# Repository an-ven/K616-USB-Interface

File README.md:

# K616 USB Interface board

Arduino based USB interface board for Keithley 616 digital electrometer. Somewhat inspired by Keithley 6162 Isolated Output and Control module, but with a modern computer interface.

## Firmware features

- Presents a common USB serial interface
- Measurement capture using hardware counter and interrupts
- Instrument control (Remote zero check, Sensitivity selection and Display hold)
- Continuous or single measurement output
- Compact and human readable output formats
- Mostly single character commands for instrument and interface control
- Interface settings can be saved to load on next power up

## Hardware features

- Optically isolated inputs and outputs
- Mounts inside the instrument with USB port accessible on the back panel
- Fits on to K6162 interface pins headers (J113, J114 and J115) on the main board

# Measurement output

Output strings consist of three parts separated by space characters: 
- a float type number representing the measured value
- units of the measured value
- instrument state indicators

In normal or "compact" output mode (selected by sending `u` command character) the number mirrors the instrument display, where sensitivity setting directly determines the number of decimal places of mantissa and the exponent is determined form range switch position. Units are also determined by range switch position. Instrument state indicators are printed as single characters:
- `N` ... Normal operation
- `O` ... Overflow
- `Z` ... Zero Check
- `R` ... Remote Zero Check
- `A` ... Auto sensitivity
- `M` ... Manual sensitivity
- `n` ... Sensitivity range number where `n={1,2,3,4,5}`
- `H` ... Display hold enabled 
- `E` ... Count error (instrument probably off)

In human friendly output mode (selected by sending `U` command character) the number of decimal places and unit prefix are determined based on what is most appropriate for currently selected range and sensitivity settings. The instrument state indicator characters get replaced by whole words separated by space characters.

## Example outputs strings

Normal operation (measuring resistance, automatic sensitivity):

    +0.993E9 Ohm NA3

Human friendly unit display (same conditions as above):

    +0.992 GOhm Normal Auto Sensitivity=3

Remote zero check enabled:

    -0.00000E-6 A ZRA1

    -0.00 nA Zero Remote Auto Sensitivity=1

Overflow condition, manual sensitivity:

    +0.2016E0 V OM2

    +201.6 mV Overflow Manual Sensitivity=2

Instrument powered off (no "gated clock" and "count now" signals detected)

    -999.9E-6 A E

    -999.9 uA Count Error

# Command set

The interface board can be controlled using mostly single character commands, exception being the sensitivity select command which consists of two characters.

## Instrument control:

`Z|z`: Remote zero check (upper case to enable, lower case to disable)

`H|h`: Instrument display hold (upper case to enable, lower case to disable)

`r[x]`: Sensitivity select, where [x] is a number representing different sensitivity settings:
- 0 ... Auto sensitivity
- 1 ... 0,01 full scale
- 2 ... 0,1 full scale
- 3 ... 1 full scale
- 4 ... 10 full scale
- 5 ... 100 full scale

## Interface control:

`S|s`: Continuous measurement output (upper case to enable, lower case to disable)

`p`: Print measurement result once

`U|u`: Human friendly output (upper case to enable, lower case to disable)

`f`: Save current interface configuration to EEPROM to load on next power cycle

`i`: Print ID string (useful when determining if the correct port is being used)

`?`: Print help message

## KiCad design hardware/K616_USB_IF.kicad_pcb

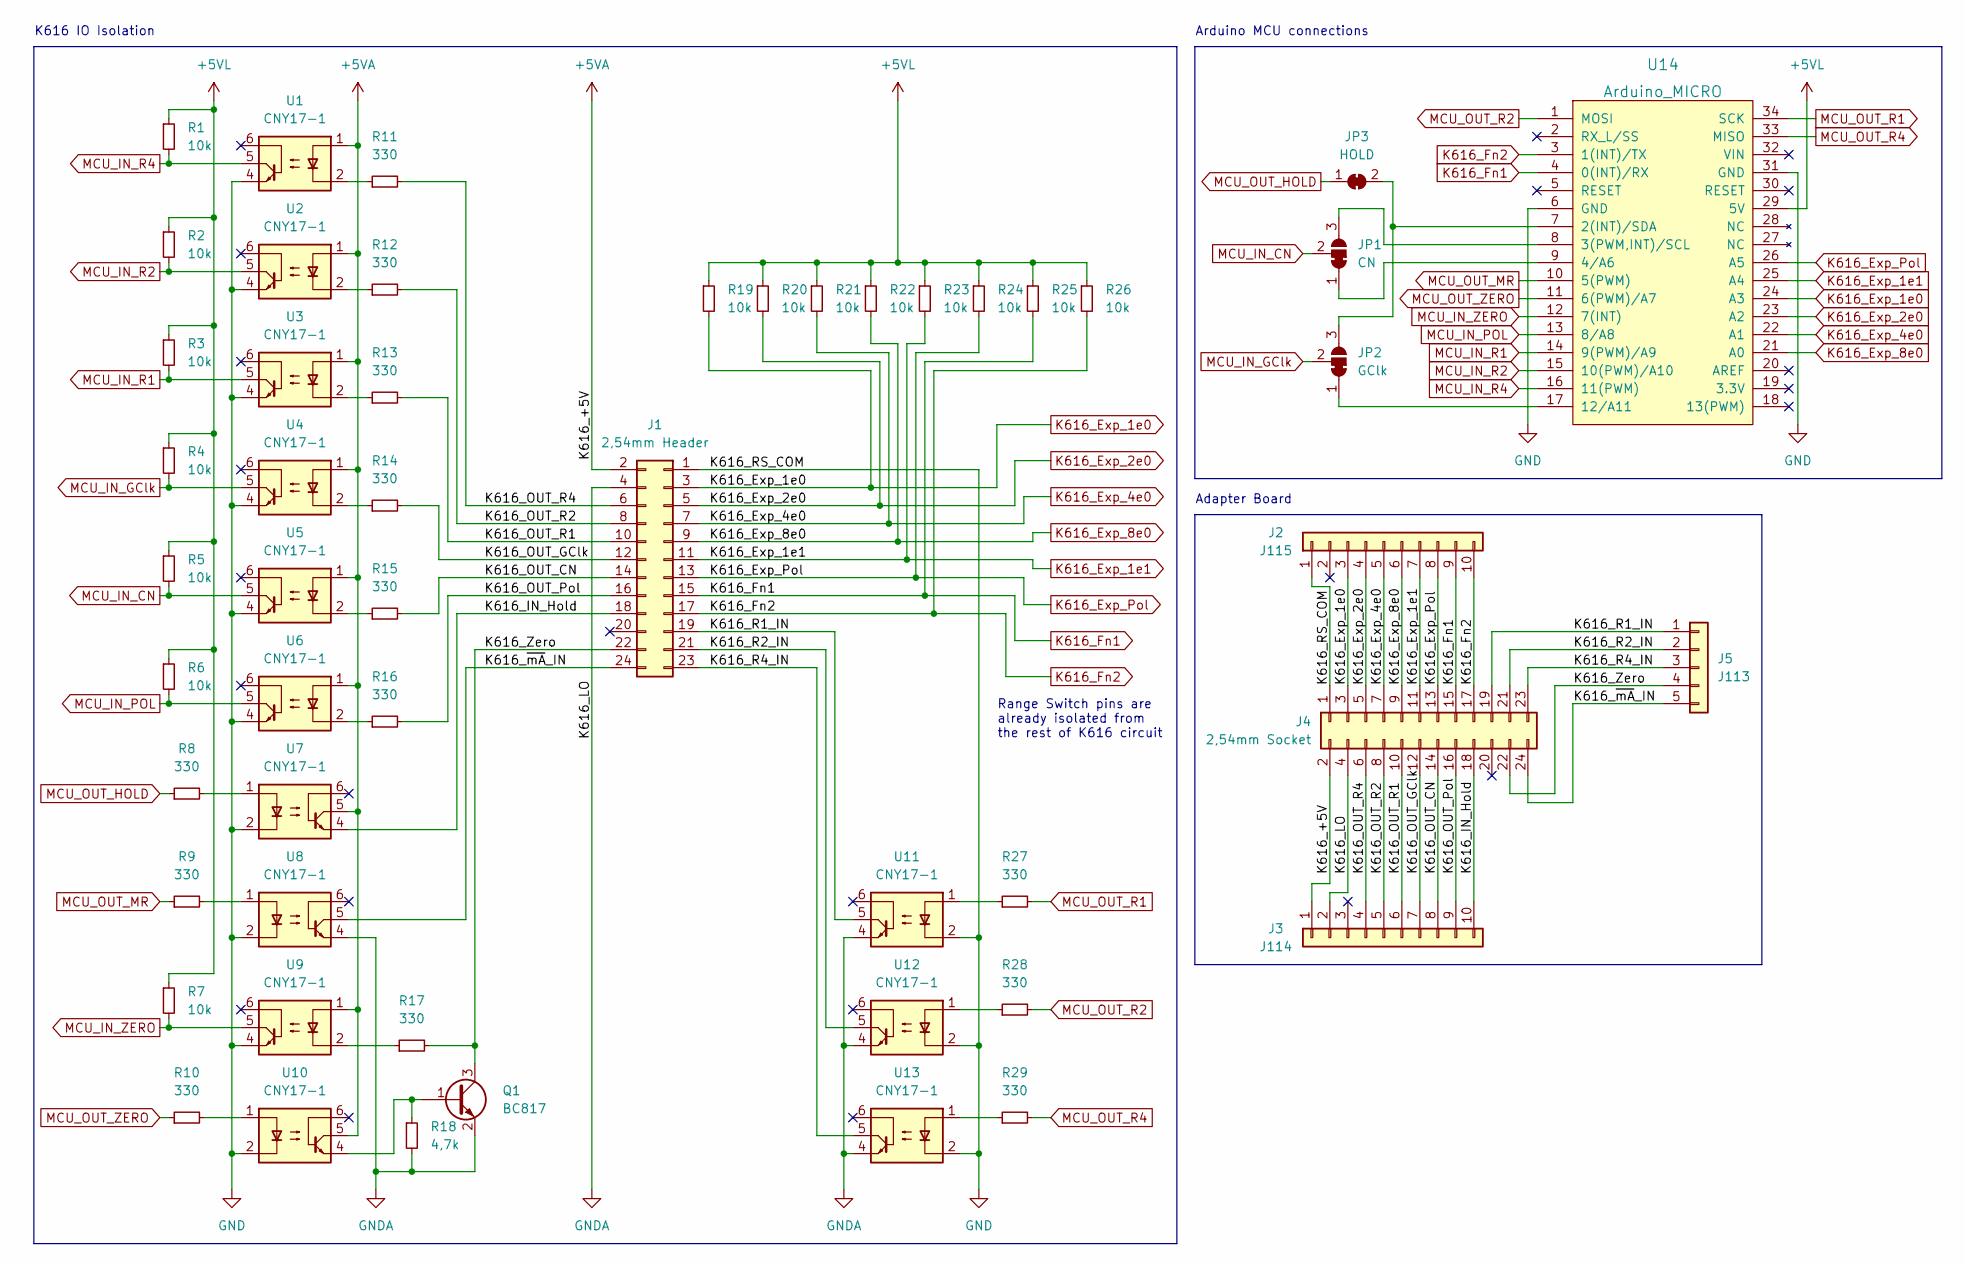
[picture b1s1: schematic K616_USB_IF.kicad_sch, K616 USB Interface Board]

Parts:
J1: 2,54mm Header; PinHeader_2x12_P2.54mm_Horizontal
J2: J115; PinSocket_1x10_P2.54mm_Vertical
J3: J114; PinSocket_1x10_P2.54mm_Vertical
J4: 2,54mm Socket; PinSocket_2x12_P2.54mm_Vertical
J5: J113; PinSocket_1x05_P2.54mm_Vertical
JP1: CN; SolderJumper-3_P1.3mm_Bridged12_RoundedPad1.0x1.5mm
JP2: GClk; SolderJumper-3_P1.3mm_Bridged12_RoundedPad1.0x1.5mm
JP3: HOLD; SolderJumper-2_P1.3mm_Bridged_RoundedPad1.0x1.5mm
Q1: BC817; SOT-23_Handsoldering
R1, R2, R3, R4, R5, R6, R7, R19, R20, R21, R22, R23, R24, R25, R26: 10k; R_0603_1608Metric_Pad0.98x0.95mm_HandSolder
R8, R9, R10, R11, R12, R13, R14, R15, R16, R17, R27, R28, R29: 330; R_0603_1608Metric_Pad0.98x0.95mm_HandSolder
R18: 4,7k; R_0603_1608Metric_Pad0.98x0.95mm_HandSolder
U1, U2, U3, U4, U5, U6, U7, U8, U9, U10, U11, U12, U13: CNY17-1; SMDIP-6_W7.62mm
U14: Arduino_MICRO; ArduinoMicro

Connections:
+5VA: J1.2, J3.1, J4.2, U1.1, U2.1, U3.1, U4.1, U5.1, U6.1, U7.5, U9.1, U10.5
+5VL: R1.1, R2.1, R3.1, R4.1, R5.1, R6.1, R7.1, R19.1, R20.1, R21.1, R22.1, R23.1, R24.1, R25.1, R26.1, U14.29 (5V)
/K616_IN_Hold: J1.18, J3.10, J4.18, U7.4
/K616_OUT_CN: J1.14, J3.8, J4.14, R15.2
/K616_OUT_GClk: J1.12, J3.7, J4.12, R14.2
/K616_OUT_Pol: J1.16, J3.9, J4.16, R16.2
/K616_OUT_R1: J1.10, J3.6, J4.10, R13.2
/K616_OUT_R2: J1.8, J3.5, J4.8, R12.2
/K616_OUT_R4: J1.6, J3.4, J4.6, R11.2
/K616_R1_IN: J1.19, J4.19, J5.1, U11.5
/K616_R2_IN: J1.21, J4.21, J5.2, U12.5
/K616_R4_IN: J1.23, J4.23, J5.3, U13.5
/K616_Zero: J1.22, J4.22, J5.4, Q1.3 (C), R17.2
/K616_~mA_IN: J1.24, J4.24, J5.5, U8.5
GND: J1.1, J2.1, J4.1, U1.4, U2.4, U3.4, U4.4, U5.4, U6.4, U7.2, U8.2, U9.4, U10.2, U11.2, U12.2, U13.2, U14.6 (GND), U14.31 (GND)
GNDA: J1.4, J3.2, J4.4, Q1.2 (E), R18.2, U8.4, U11.4, U12.4, U13.4
K616_Exp_1e0: J1.3, J2.3, J4.3, R19.2, U14.24 (A3)
K616_Exp_1e1: J1.11, J2.7, J4.11, R23.2, U14.25 (A4)
K616_Exp_2e0: J1.5, J2.4, J4.5, R20.2, U14.23 (A2)
K616_Exp_4e0: J1.7, J2.5, J4.7, R21.2, U14.22 (A1)
K616_Exp_8e0: J1.9, J2.6, J4.9, R22.2, U14.21 (A0)
K616_Exp_Pol: J1.13, J2.8, J4.13, R24.2, U14.26 (A5)
K616_Fn1: J1.15, J2.9, J4.15, R25.2, U14.4 (0(INT)/RX)
K616_Fn2: J1.17, J2.10, J4.17, R26.2, U14.3 (1(INT)/TX)
MCU_IN_CN: JP1.2 (C), R5.2, U5.5
MCU_IN_GClk: JP2.2 (C), R4.2, U4.5
MCU_IN_POL: R6.2, U6.5, U14.13 (8/A8)
MCU_IN_R1: R3.2, U3.5, U14.14 (9(PWM)/A9)
MCU_IN_R2: R2.2, U2.5, U14.15 (10(PWM)/A10)
MCU_IN_R4: R1.2, U1.5, U14.16 (11(PWM))
MCU_IN_ZERO: R7.2, U9.5, U14.12 (7(INT))
MCU_OUT_HOLD: JP3.1 (A), R8.1
MCU_OUT_MR: R9.1, U14.10 (5(PWM))
MCU_OUT_R1: R27.2, U14.34 (SCK)
MCU_OUT_R2: R28.2, U14.1 (MOSI)
MCU_OUT_R4: R29.2, U14.33 (MISO)
MCU_OUT_ZERO: R10.1, U14.11 (6(PWM)/A7)
unnamed: JP1.1 (A), U14.9 (4/A6)
unnamed: JP1.3 (B), U14.8 (3(PWM,INT)/SCL)
unnamed: JP2.1 (A), U14.17 (12/A11)
unnamed: JP2.3 (B), JP3.2 (B), U14.7 (2(INT)/SDA)
unnamed: Q1.1 (B), R18.1, U10.4
unnamed: R8.2, U7.1
unnamed: R9.2, U8.1
unnamed: R10.2, U10.1
unnamed: R11.1, U1.2
unnamed: R12.1, U2.2
unnamed: R13.1, U3.2
unnamed: R14.1, U4.2
unnamed: R15.1, U5.2
unnamed: R16.1, U6.2
unnamed: R17.1, U9.2
unnamed: R27.1, U11.1
unnamed: R28.1, U12.1
unnamed: R29.1, U13.1

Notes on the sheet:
Range Switch pins are already isolated from the rest of K616 circuit
Adapter Board
Arduino MCU connections
K616 IO Isolation

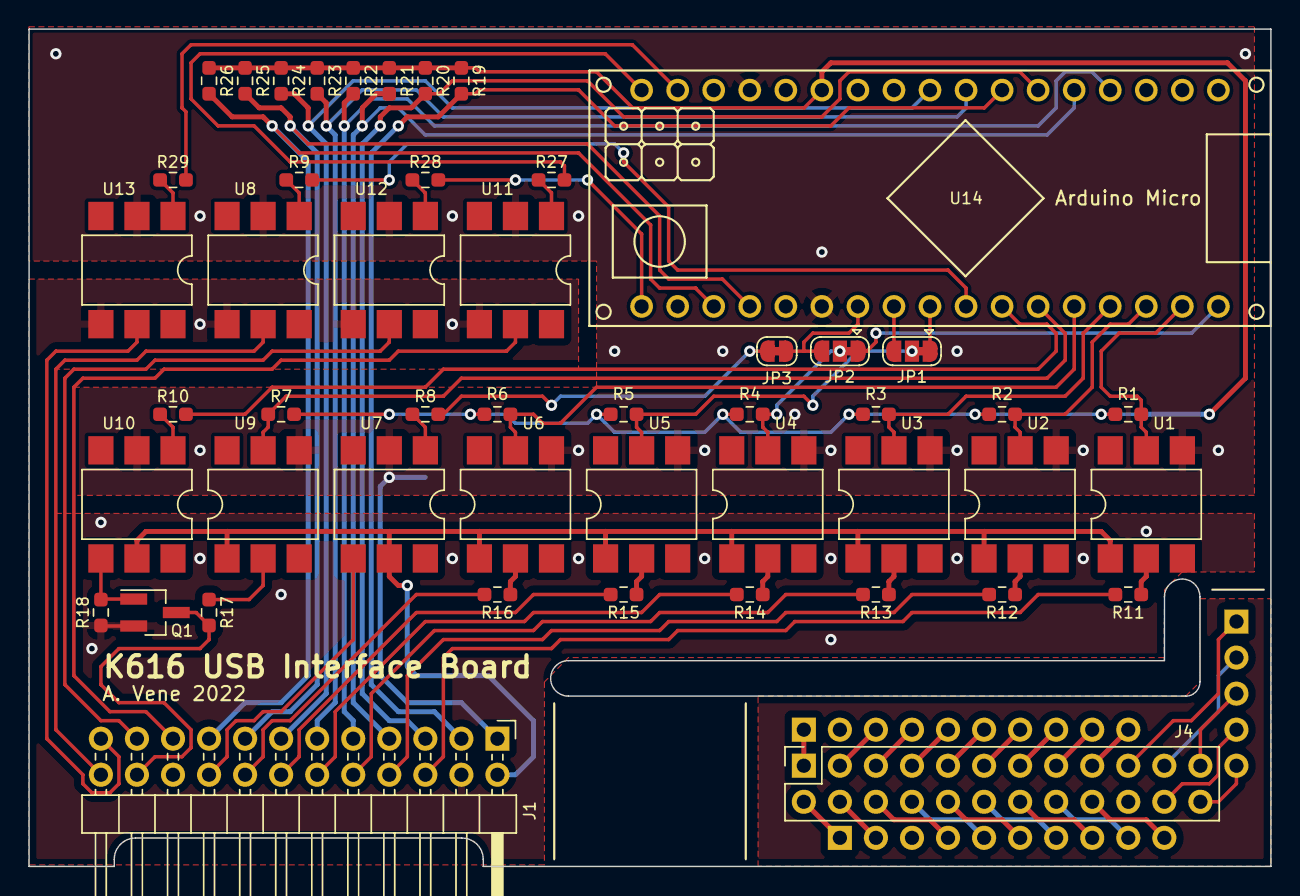
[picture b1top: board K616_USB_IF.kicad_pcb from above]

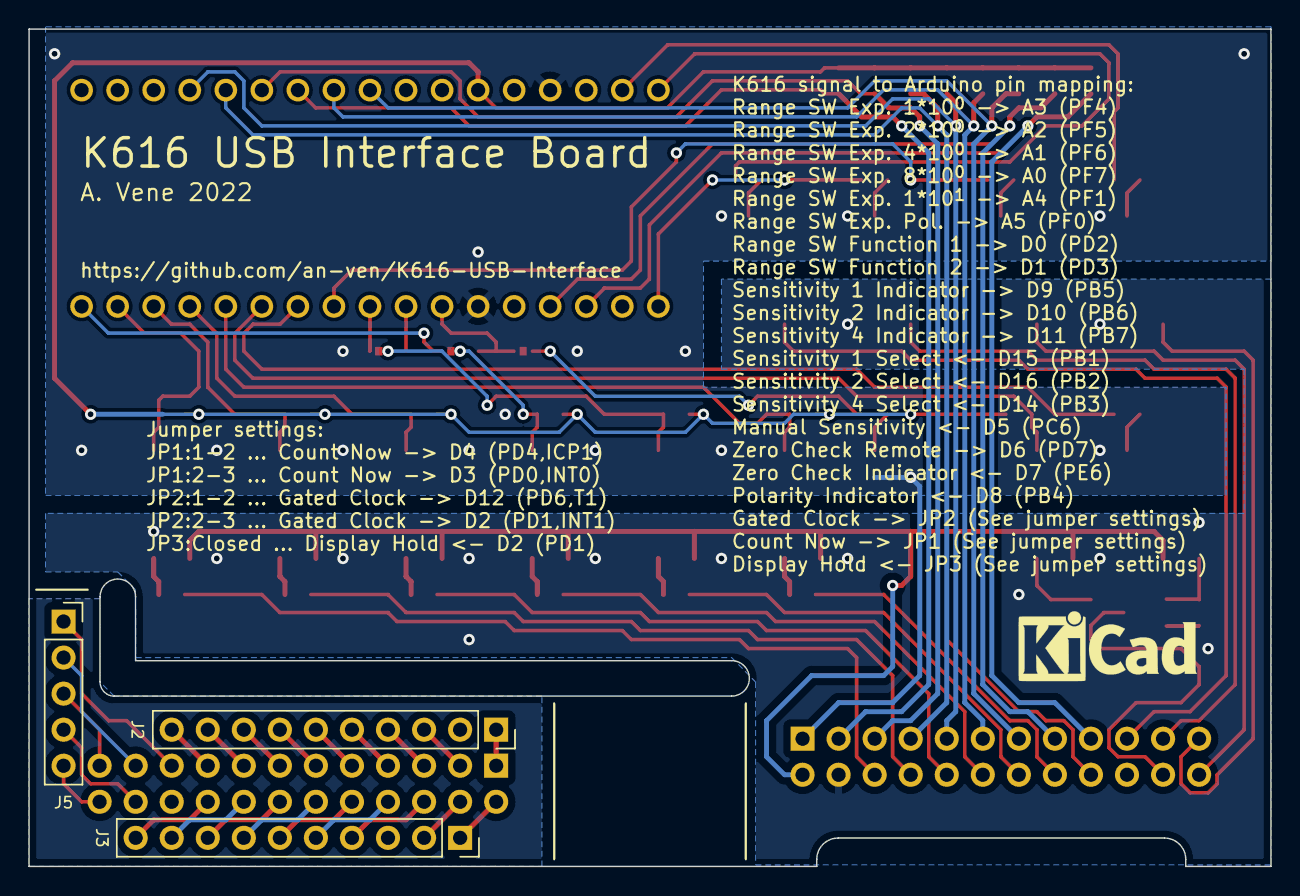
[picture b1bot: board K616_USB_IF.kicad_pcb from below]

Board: 2 copper layers, 87.5 x 59.0 mm, 52 parts (3 on the bottom side), 55 nets.

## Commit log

2022-09-13 Actual first commit of source files
2022-09-13 Add top image to README.md
2022-10-28 Add sensitivity indicator to output strings
2022-11-03 Add some python scripts for reading data from interface
